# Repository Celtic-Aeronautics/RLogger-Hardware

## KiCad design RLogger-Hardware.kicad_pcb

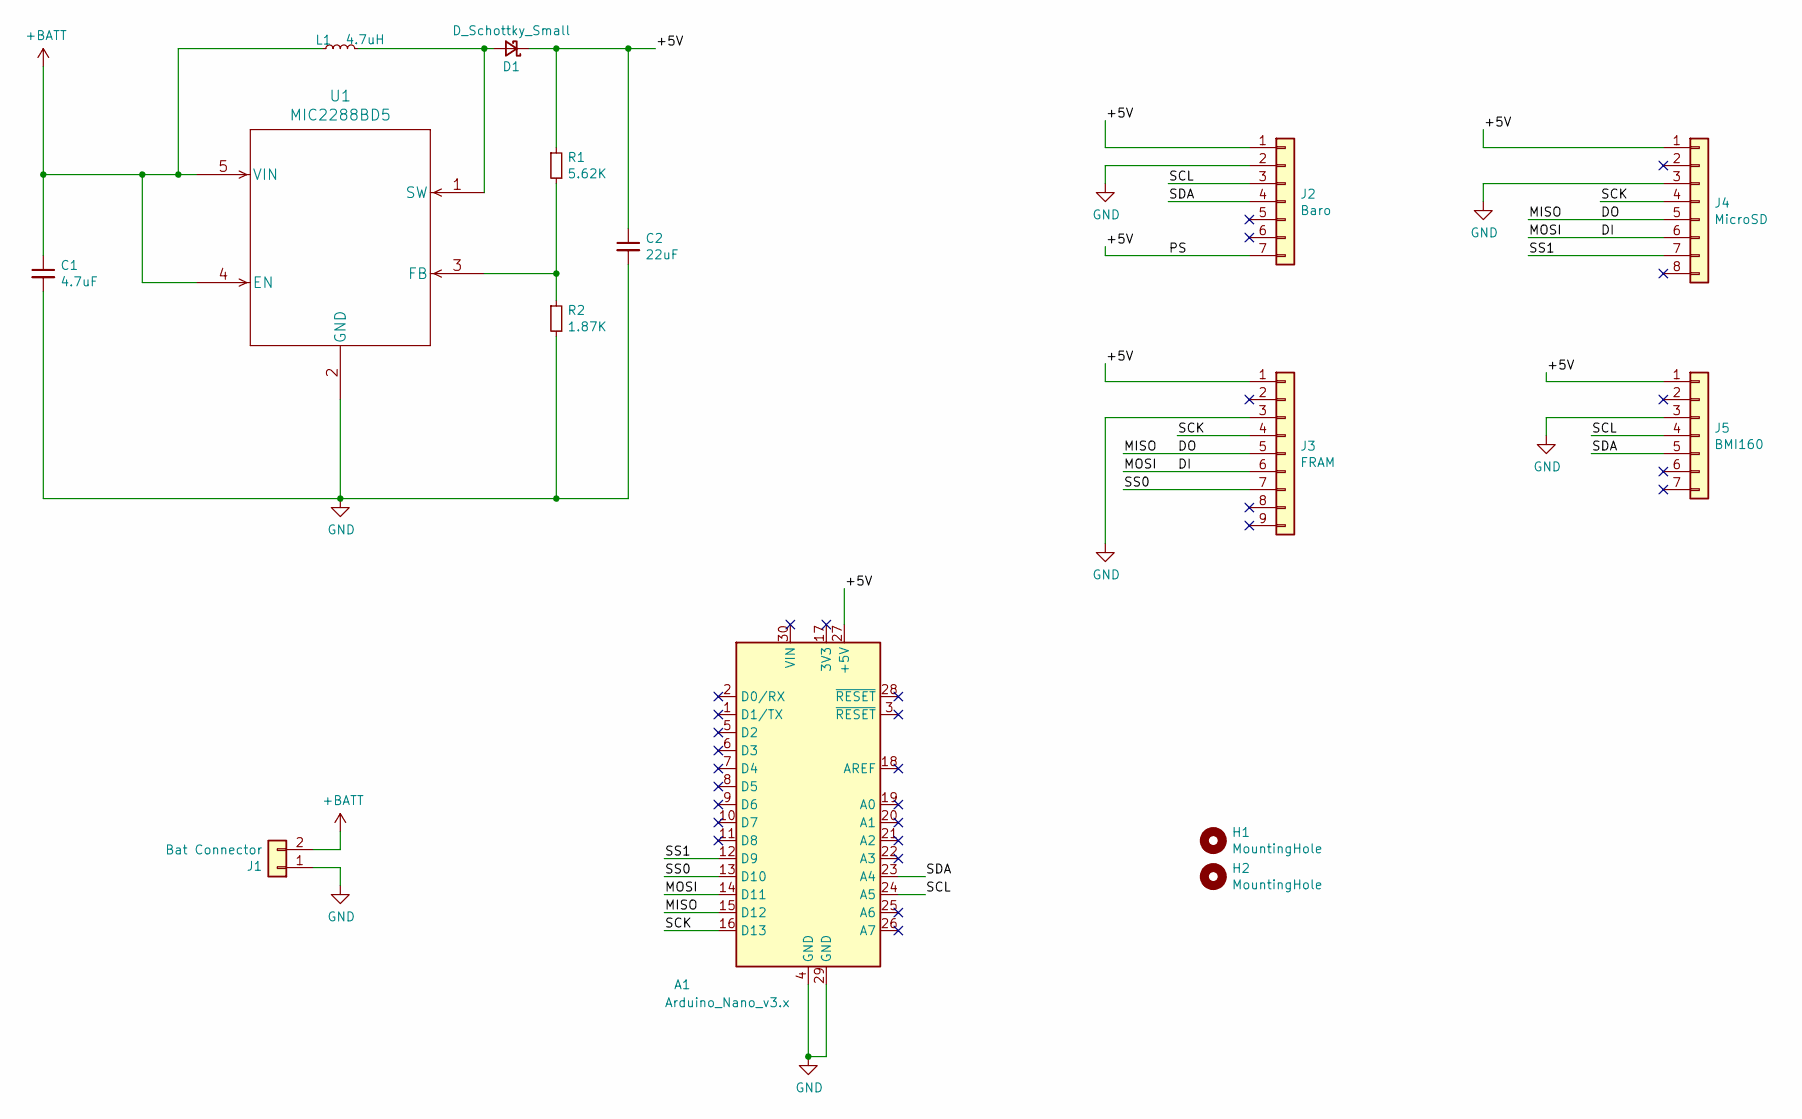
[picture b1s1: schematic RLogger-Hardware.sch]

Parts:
A1: Arduino_Nano_v3.x; Arduino_Nano
C1: 4.7uF; C_0805_2012Metric_Pad1.15x1.40mm_HandSolder
C2: 22uF; C_1206_3216Metric_Pad1.33x1.80mm_HandSolder
D1: D_Schottky_Small; D_Powermite_AK
H1, H2: MountingHole; MountingHole_2.2mm_M2
J1: Bat Connector; PinSocket_1x02_P2.54mm_Vertical
J2: Baro; PinSocket_1x07_P2.54mm_Vertical
J3: FRAM; PinSocket_1x09_P2.54mm_Vertical
J4: MicroSD; PinSocket_1x08_P2.54mm_Vertical
J5: BMI160; PinSocket_1x07_P2.54mm_Vertical
L1: 4.7uH; L_0805_2012Metric_Pad1.05x1.20mm_HandSolder
R1: 5.62K; R_0805_2012Metric_Pad1.15x1.40mm_HandSolder
R2: 1.87K; R_0805_2012Metric_Pad1.15x1.40mm_HandSolder
U1: MIC2288BD5; SOT-23-5_HandSoldering

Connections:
+BATT: C1.1, J1.2, L1.1, U1.4 (EN), U1.5 (VIN)
/+5V: A1.27 (+5V), C2.1, D1.1 (K), J2.1, J2.7, J3.1, J4.1, J5.1, R1.1
/DI: A1.14 (D11), J3.6, J4.6
/DO: A1.15 (D12), J3.5, J4.5
/SCK: A1.16 (D13), J3.4, J4.4
/SCL: A1.24 (A5), J2.3, J5.4
/SDA: A1.23 (A4), J2.4, J5.5
/SS0: A1.13 (D10), J3.7
/SS1: A1.12 (D9), J4.7
GND: A1.4 (GND), A1.29 (GND), C1.2, C2.2, J1.1, J2.2, J3.3, J4.3, J5.3, R2.2, U1.2 (GND)
unnamed: D1.2 (A), L1.2, U1.1 (SW)
unnamed: R1.2, R2.1, U1.3 (FB)

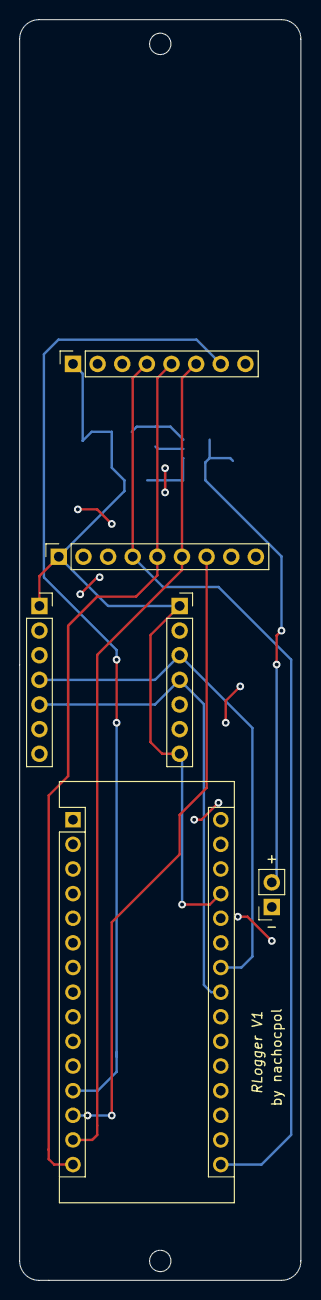
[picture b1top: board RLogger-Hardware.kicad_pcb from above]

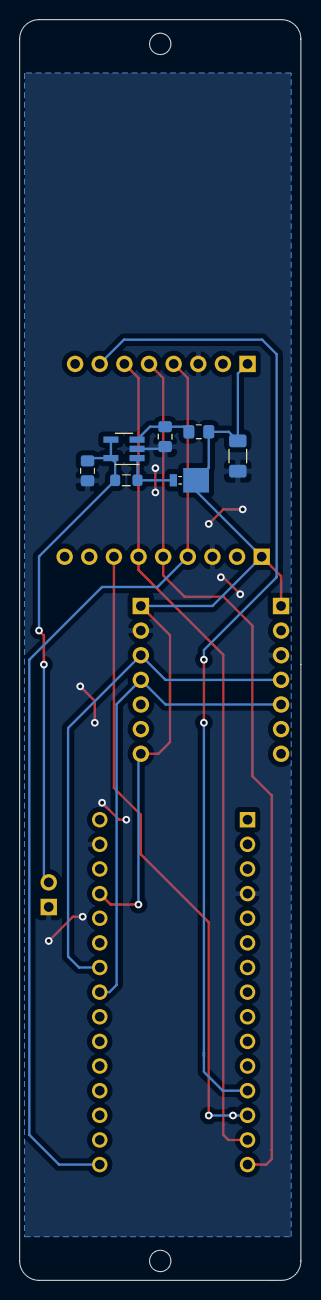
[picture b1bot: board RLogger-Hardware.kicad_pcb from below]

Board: 2 copper layers, 29.0 x 130.0 mm, 15 parts (7 on the bottom side), 12 nets.

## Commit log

2021-05-03 Initial drop
2021-05-03 Assigned footprints.
2021-05-03 Working on the PCB layout
2021-05-03 PCB done :o
2021-05-06 Added mounting holes. Updated PCB layout. Generated fabrication files.
2021-05-13 Final cleanup.
